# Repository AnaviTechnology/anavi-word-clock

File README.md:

# ANAVI Word Clock

Open source 8x8 NeoPixel word clock.

# Case

The case is designed using the free and open-source tool OpenSCAD and requires a custom stencil font.

## Installing the Stencil Font on Ubuntu

Follow the steps below to install the Arial stencil font on an Ubuntu Linux distribution:

*  Copy the font file:

```
sudo mkdir /usr/share/fonts/anavi
sudo cp Arial-BoldStencila.ttf /usr/share/fonts/anavi
sudo chmod -R --reference=/usr/share/fonts/opentype /usr/share/fonts/anavi
```

NOTE: Root privileges are required to install fonts system-wide.

* Update the font cache:

```
sudo fc-cache -fv
```

* Verify the installation:

```
fc-list | grep -i arial
```

The font should appear in the output list. The font name reported by fc-list must be used exactly in the OpenSCAD text() function.

* Launch OpenSCAD

Restart OpenSCAD if it was already running so it can detect the newly installed font.

# License

The project is released under the [Creative Commons Attribution-ShareAlike 4.0 International (CC BY-SA 4.0)](https://creativecommons.org/licenses/by-sa/4.0/).

Note: This is a human-readable summary of (and not a substitute for) the [license](https://creativecommons.org/licenses/by-sa/4.0/legalcode).

You are free to:

Share — copy and redistribute the material in any medium or format Adapt — remix, transform, and build upon the material for any purpose, even commercially. The licensor cannot revoke these freedoms as long as you follow the license terms. Under the following terms:

Attribution — You must give appropriate credit, provide a link to the license, and indicate if changes were made. You may do so in any reasonable manner, but not in any way that suggests the licensor endorses you or your use. ShareAlike — If you remix, transform, or build upon the material, you must distribute your contributions under the same license as the original. No additional restrictions — You may not apply legal terms or technological measures that legally restrict others from doing anything the license permits. Notices:

You do not have to comply with the license for elements of the material in the public domain or where your use is permitted by an applicable exception or limitation. No warranties are given. The license may not give you all of the permissions necessary for your intended use. For example, other rights such as publicity, privacy, or moral rights may limit how you use the material.

You will have to provide a link to the original creator of the project http://www.anavi.technology on any documentation or website.

Credit can be attributed through a link to the creator website: http://www.anavi.technology

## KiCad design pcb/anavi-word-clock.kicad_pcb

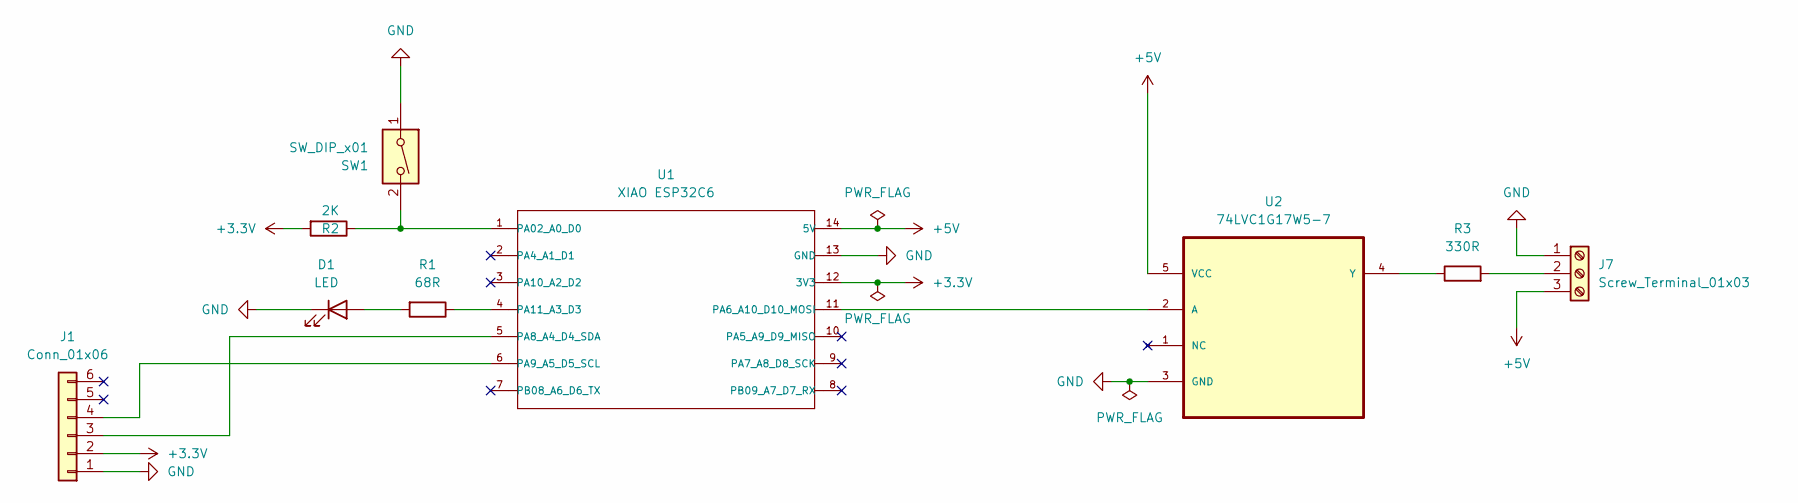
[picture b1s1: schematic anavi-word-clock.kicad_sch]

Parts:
D1: LED; LED_1206_3216Metric
J1: Conn_01x06; PinSocket_1x06_P2.54mm_Horizontal
J7: Screw_Terminal_01x03; TerminalBlock_Phoenix_MKDS-1,5-3_1x03_P5.00mm_Horizontal
R1: 68R; R_0603_1608Metric_Pad0.98x0.95mm_HandSolder
R2: 2K; R_0603_1608Metric_Pad0.98x0.95mm_HandSolder
R3: 330R; R_0603_1608Metric_Pad0.98x0.95mm_HandSolder
SW1: SW_DIP_x01; SW_TL1105SF160Q_EWI
U1: XIAO ESP32C6; XIAO-ESP32-C6-SMD
U2: 74LVC1G17W5-7; SOT95P280X145-5N; MPN 74LVC1G17W5-7

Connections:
+3.3V: J1.2, R2.2, U1.12 (3V3)
+5V: J7.3, U1.14 (5V), U2.5 (VCC)
GND: D1.1 (K), J1.1, J7.1, SW1.1, U1.13 (GND), U2.3 (GND)
unnamed: D1.2 (A), R1.2
unnamed: J1.3, U1.5 (PA8_A4_D4_SDA)
unnamed: J1.4, U1.6 (PA9_A5_D5_SCL)
unnamed: J7.2, R3.2
unnamed: R2.1, SW1.2, U1.1 (PA02_A0_D0)
unnamed: U1.11 (PA6_A10_D10_MOSI), U2.2 (A)
unnamed: R1.1, U1.4 (PA11_A3_D3)
unnamed: R3.1, U2.4 (Y)

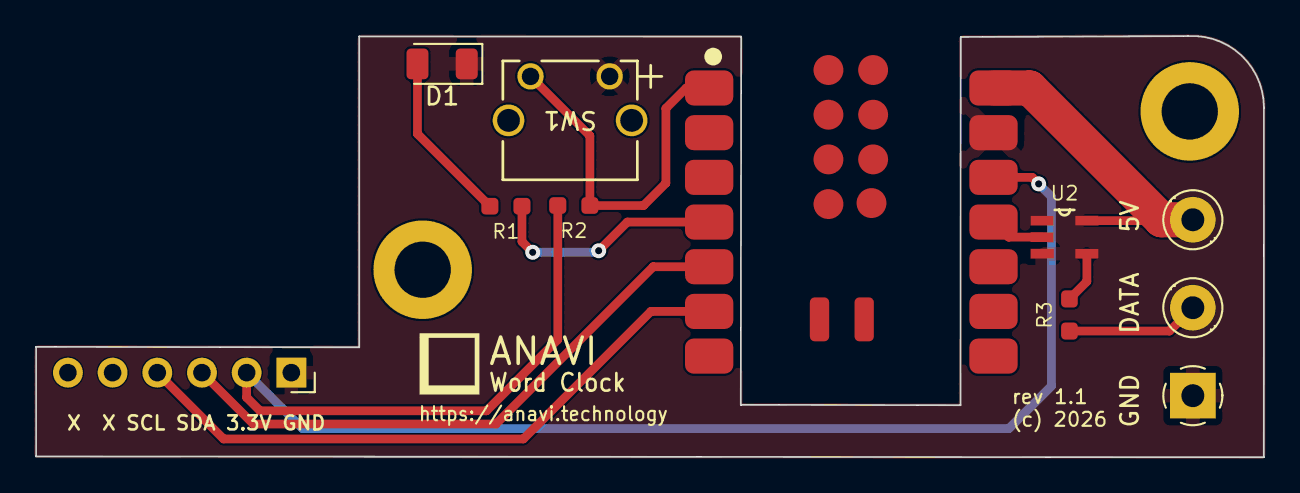
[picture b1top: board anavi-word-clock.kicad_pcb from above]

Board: 2 copper layers, 69.8 x 23.9 mm, 9 parts (0 on the bottom side), 11 nets.

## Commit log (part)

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2025-12-29 ANAVI Word Clock
    Initialize the project with README.md and .gitignore.
2025-12-29 case: Add anavi-word-clock-top.scad
    OpenSCAD design file for the top part with letters.
2025-12-30 case: Add stencil font
    Add Arial-BoldStencila.ttf suitable for 3D printing. It is a
    stencil font that is a typeface designed so that the inner parts
    of letters are connected by bridges, allowing the letters to be
    cut or painted without pieces falling out.
2025-12-30 README.md: Install stencil font
    Add the exact steps how to install the stencil font on Ubuntu.
2025-12-30 case: Use stencil font
    Modify the top of the case to use the appropriate stencil font.
2025-12-30 case/anavi-word-clock-top.scad: Add grid
    Add 8x8 grid with a cell for each NeoPixel.
2025-12-30 case/anavi-word-clock-top.scad: Reduce size
    Reduce size from 100mm to 98mm. The top part is 2 mm shorter than
    the bottom, aka 1 mm on each side. So the whole case will be 10cm.
2025-12-30 case: Add anavi-word-clock-back.scad
    Add OpenSCAD design for the back cover of the clock.
2025-12-30 case/anavi-word-clock-top.scad: Grid height
    Reduce grid height to 4mm and adjust the position.
2025-12-31 case/anavi-word-clock-diffuser.scad: Add
    Add a small plate that should act as a light diffuser.
2026-01-01 case/anavi-word-clock-panel.scad: Add
    Add a panel to hold the NeoPixel matrix.
2026-01-01 case/anavi-word-clock-grid.scad: Add
    Add a 3D model of a grid between the NeoPixel panel (in its cover)
    and the diffuser.
2026-01-01 case/anavi-word-clock-top.scad: Mounting holes
    Add mounting holes in the middle to hold the NeoPixel panel.
2026-01-03 case/anavi-word-clock-panel.scad: Add hooks
    Add four hooks to firmly attach the panel with NeoPixels to the
    front part of the clock.
2026-01-03 case/anavi-word-clock-top.scad: Add hooks
    Increase grid height to 5mm and add four hooks to firmly attach
    the NeoPixel panel cover to the front of the word clock.
2026-01-03 case/anavi-word-clock-grid.scad: Adjust size
    Increase the grid height to 5mm, adjust the total size to 81mm.
2026-01-04 anavi-word-clock-back.scad: PCB mounting holes
    Add two PCB mounting holes for ANAVI Miracle Emitter.
2026-01-04 case/anavi-word-clock-panel.scad: Hook positions
    Adjust the hook positions so they align precisely with the top
    plate.
2026-01-05 case/anavi-word-clock-back.scad: Adjust position
    Adjust the vertical position of the mounting holes for the printed
    circuit board, a.k.a for ANAVI Miracle Emitter.
2026-01-05 case/anavi-word-clock-back.stl: Add
    Add STL for the back part of ANAVI Word Clock.
2026-01-05 case/anavi-word-clock-back: Increase to 55mm
    Increase from 50mm to 55mm because of the M3 50mm standard screws.
2026-01-06 case/anavi-word-clock-back.scad: Reduce to 45mm
    Following some optimizations of the from we can reduce the depth
    to 45mm for ANAVI Miracle Emitter.
2026-01-06 case/anavi-word-clock-grid.scad: Diffuser
    Generate either grid or a diffuser with the same code.
2026-01-06 case/anavi-word-clock-top.scad: No grid
    Don't draw grid because it will be a separate part.
2026-01-06 case/anavi-word-clock-panel.scad: Hooks height
    Reduce the height of the hooks to 8mm.
2026-01-11 pcb: ANAVI Word Clock PCB
    Initial version of a printed circuit board based on ANAVI Miracle
    Emitter with various modifications to make it specific for ANAVI
    Word Clock.
2026-06-27 anavi-word-clock-top.scad: Increase hole depth
    Increase the inner hole depth for M3 brass threaded inserts from
    2 mm to 4 mm.
2026-06-27 anavi-word-clock-grid-with-diffuser.3mf: Add file
    Add .3mf file that combines black grid with white diffuser.
2026-06-28 anavi-word-clock-back.stl: Set height to 45mm
    Reduce the height to 45mm.
2026-06-28 anavi-word-clock-grid.scad: Increase cell height
    Increase the height of each cell in the grid from 0.5 to 1.
2026-06-28 anavi-word-clock-panel.stl: Add file
    Add STL for the internal part that holds the NeoPixel LED panel.
2026-06-29 anavi-word-clock-grid-with-diffuser.3mf: Order
    Adjust order to start with white for better results.

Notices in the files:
pcb/anavi-word-clock.kicad_pcb:
(c) 2026
